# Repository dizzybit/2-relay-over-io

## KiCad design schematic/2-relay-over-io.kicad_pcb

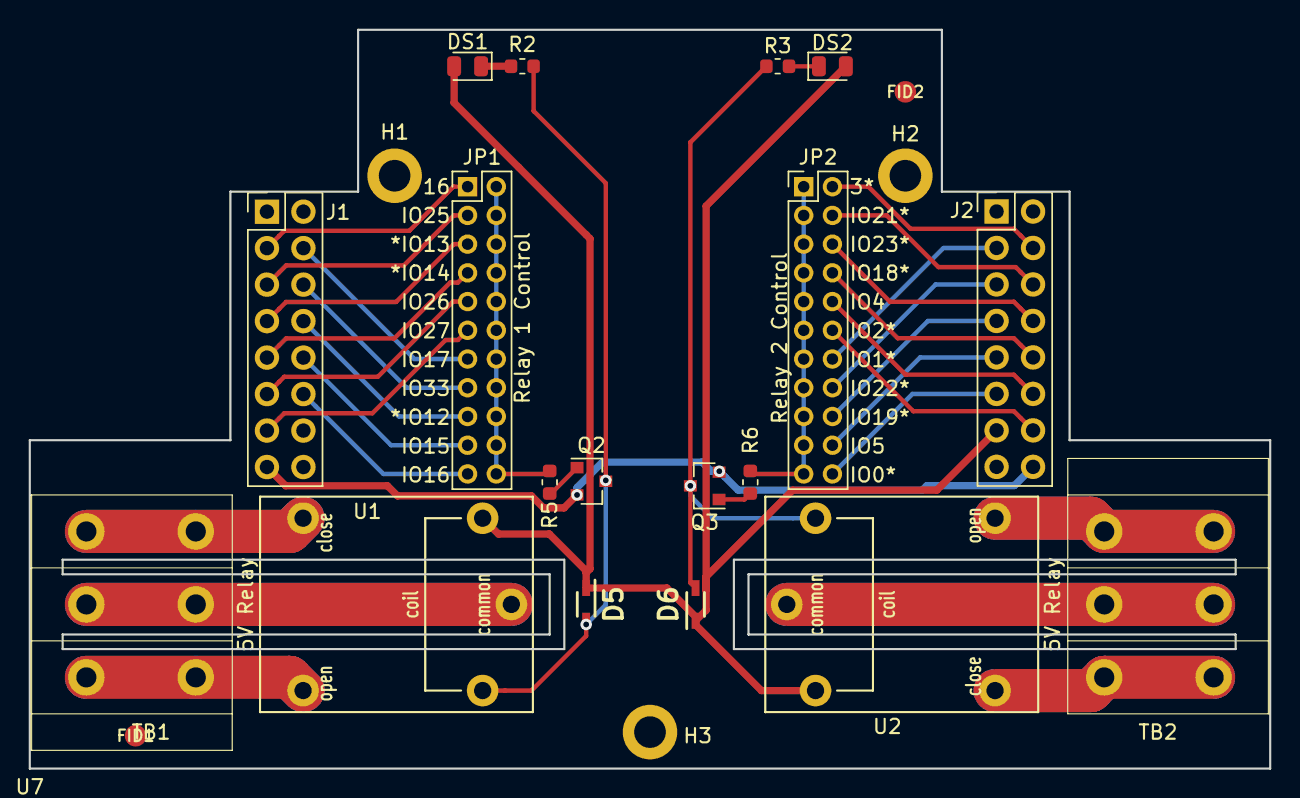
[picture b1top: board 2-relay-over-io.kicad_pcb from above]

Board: 2 copper layers, 86.4 x 51.4 mm, 25 parts (1 on the bottom side), 38 nets.

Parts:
D5, D6: BAT20JFILM; SOD2512X113N
DS1, DS2: LED-BLUE; LED_0805_2012Metric
FID1, FID2: FIDUCIAL-1.5mm
H1, H2, H3: MountingHole; MountingHole_2.2mm_M2_DIN965_Pad
J1, J2: Conn_02x08_Odd_Even; PinHeader_2x08_P2.54mm_Vertical
JP1, JP2: Conn_02x11_Odd_Even; PinHeader_2x11_P2.00mm_Vertical
Q2, Q3: BC817; SOT-23
R2, R3, R5, R6: R330; R_0603_1608Metric
TB1, TB2: WJ142R-5.08-3P
U1, U2: SONGLE_5V_relay; SONGLE_5V_Relay
U6: DizzyBITLogo; DizzyBIT_silk_20
U7: DizzyBIT-Layout; DizzyBit-Din Rail Module

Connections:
EXT_5V: D5.1, D6.1, DS1.2, DS2.2, J2.13, U1.1, U2.1
GND: J1.15, J2.16, Q2.2, Q3.2
HSPI_CLK: J1.9, JP1.7
HSPI_MISO: J1.8, JP1.17
HSPI_MOSI: J1.7, JP1.5
I2C_SCL: J2.5, JP2.16
I2C_SDA: J2.6, JP2.4
IO0: J2.11, JP2.22
IO1: J2.3, JP2.14
IO2: J2.14, JP2.12
IO3: J2.4, JP2.2
IO4: J2.12, JP2.10
IO5: J2.9, JP2.20
IO15: J1.10, JP1.19
IO16: J1.3, JP1.1
IO17: J1.4, JP1.13
IO25: J1.5, JP1.3
IO26: J1.11, JP1.9
IO27: J1.13, JP1.11
IO32: J1.12, JP1.21
IO33: J1.6, JP1.15
unnamed: D5.2, Q2.3, R2.1, U1.2
unnamed: D6.2, Q3.3, R3.1, U2.2
unnamed: DS1.1, R2.2
unnamed: DS2.1, R3.2
unnamed: Q2.1, R5.2
unnamed: Q3.1, R6.2
unnamed: TB1.1, U1.5
unnamed: TB1.2, U1.3
unnamed: TB1.3, U1.4
unnamed: TB2.1, U2.5
unnamed: TB2.2, U2.3
unnamed: TB2.3, U2.4
RELAY1_CTR: JP1.2, JP1.4, JP1.6, JP1.8, JP1.10, JP1.12, JP1.14, JP1.16, JP1.18, JP1.20, JP1.22, R5.1
RELAY2_CTR: JP2.1, JP2.3, JP2.5, JP2.7, JP2.9, JP2.11, JP2.13, JP2.15, JP2.17, JP2.19, JP2.21, R6.1
VSPI_CLK: J2.10, JP2.8
VSPI_MISO: J2.7, JP2.18
VSPI_MOSI: J2.8, JP2.6

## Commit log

2019-09-27 Work in progress
2019-09-30 Updated according to standard module design
2019-10-02 Updated 3.3v position and tracks
2019-10-02 Changed Connector designators
2019-10-04 Added 3D and Gerber files
2019-10-28 Changed the relay footprint to have bigger holes
2019-12-20 Major Update. Changed pin configuration and board outline. Relays now use the 5V load in order to avoid stressing the regulator.
